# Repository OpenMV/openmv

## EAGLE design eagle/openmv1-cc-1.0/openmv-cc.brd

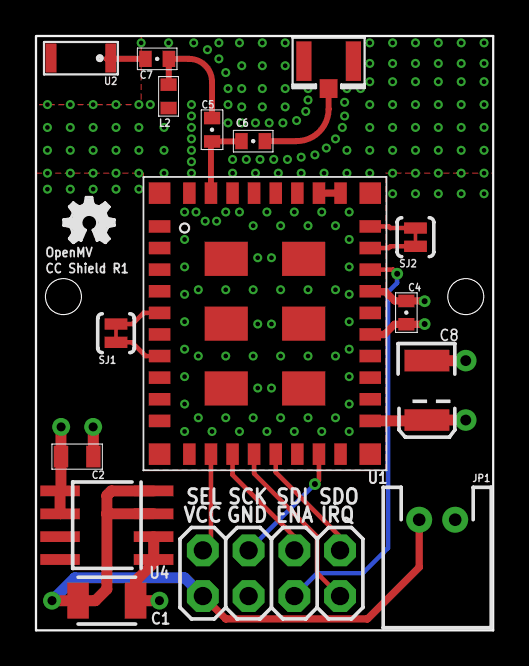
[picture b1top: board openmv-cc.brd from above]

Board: 4 copper layers, 25.4 x 33.0 mm, 17 parts (0 on the bottom side), 18 nets.

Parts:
C1: 47uF; 1210
C2: 10uF; 0805
C4: 1uF; 0402-CAP
C5, C6: 10pF; 0402-CAP
C7: 2.2pF; 0402-CAP
C8: 100uF; EIA3528
JP1: JP3; JST-2-PTH
L2: 2.2nH; C0402
LOGO1: OSHW_LOGO_FILLX0100-NT; OSHW_FILLX100_NOTEXT
SJ1, SJ2: SOLDERJUMPERTRACE; SJ_2S-TRACE
U1: CC3000
U2: ANT-YAGEO; ANTENNA
U3: U.FL
U4: TPS768; SOIC8
U5: OPENMV

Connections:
CC_CS: U1.P$12, U5.7
CC_EN: U1.P$26, U5.4
CC_IRQ: U1.P$14, U5.2
CC_MISO: U1.P$13, U5.3
CC_MOSI: U1.P$15, U5.1
CC_SCLK: U1.P$17, U5.5
GND: C1.2, C2.2, C4.2, C8.C, JP1.1, L2.2, U1.P$1, U1.P$9, U1.P$10, U1.P$11, U1.P$16, U1.P$18, U1.P$20, U1.P$21, U1.P$22, U1.P$25, U1.P$31, U1.P$32, U1.P$33, U1.P$34, U1.P$36, U1.P$37, U1.P$38, U1.P$39, U1.P$40, U1.P$41, U1.P$42, U1.P$43, U1.P$44, U1.P$45, U1.P$46, U3.P$1, U3.P$2, U4.1, U4.2, U5.6
unnamed: C5.1, C7.2, L2.1
unnamed: SJ1.2, U1.P$5
unnamed: SJ2.2, U1.P$28
unnamed: SJ1.1, U1.P$7
unnamed: SJ2.1, U1.P$27
unnamed: C5.2, C6.2, U1.P$35
unnamed: U1.P$29, U1.P$30
unnamed: C7.1, U2.P$1
unnamed: C6.1, U3.P$3
VCC: C2.1, C4.1, C8.A, U1.P$19, U1.P$23, U4.5, U4.6
VIN: C1.1, JP1.2, U4.3, U4.4, U5.8

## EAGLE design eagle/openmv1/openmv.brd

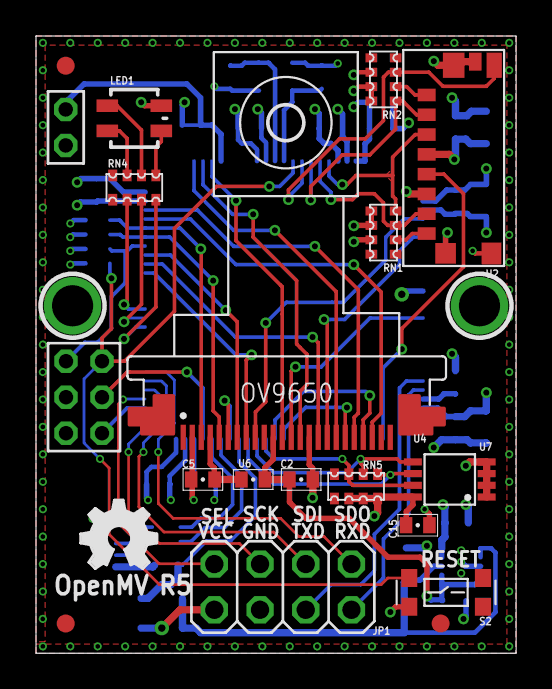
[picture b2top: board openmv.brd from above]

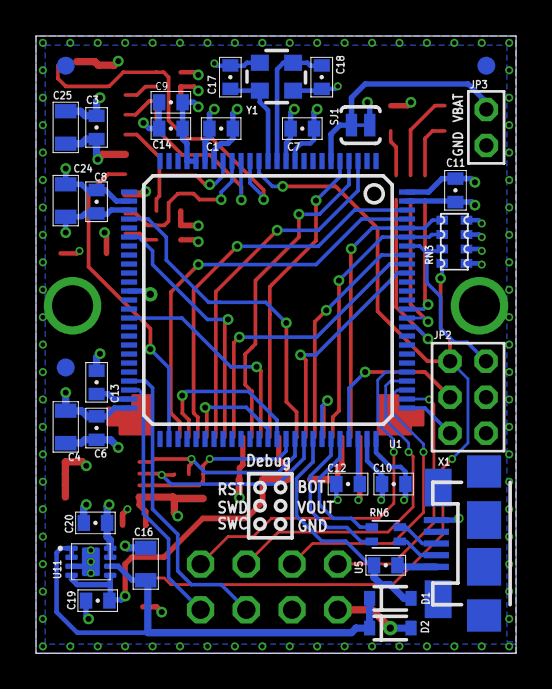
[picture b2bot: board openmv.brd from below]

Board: 4 copper layers, 26.7 x 34.3 mm, 52 parts (34 on the bottom side), 59 nets.

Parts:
C1, C3, C6, C7, C8, C9, C10, C11, C15: 0.1uF; 0402-CAP
C2, C5: 4.7uF; 0402-CAP
C4, C16, C24: 10uF; 0805
C12, C13: 2.2uF; 0402-CAP
C14, C19, C20: 1uF; 0402-CAP
C17, C18: 12pF; 0402-CAP
C25: 22uF; 0805
D1, D2: SOD-323
JP1: 2X04
JP2: 2X03
JP3: PINHD-1X2; 1X2
LED1: LED-TRICOLOR; LED-TRICOLOR-SMD
LOGO1: OSHW_LOGO_FILLX0150-NT; OSHW_FILLX150_NOTEXT
RN1, RN2, RN3, RN5: 10K; CAT16
RN4: 330R; CAT16
RN6: 27R; EXBV4V
S2: SWITCHKMR442G; KMR442G
SJ1: SOLDERJUMPERTRACE; SJ_2S-TRACE
U1: OV9650
U2: USD-47571
U4: STM32F407LQFP100; LQFP100
U5, U6: BEAD; 0402-CAP
U7: 24FC128; MSOP8
U11: ADP222; LFCSP8
U$3, U$4, U$5, U$7, U$9, U$10: FIDUCIAL; FIDUCIAL_1MM
X1: USB-MICROB
Y1: CRYSTAL-2.5X2.0

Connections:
2.8V: C2.1, C19.1, U1.P$11, U6.2, U11.4, U11.5
BOOT0: JP2.2, RN3.7, U4.94
DCMI0: U1.P$19, U4.63
DCMI1: U1.P$21, U4.64
DCMI2: U1.P$22, U4.97
DCMI3: U1.P$20, U4.98
DCMI4: U1.P$18, U4.3
DCMI5: U1.P$16, U4.92
DCMI6: U1.P$14, U4.4
DCMI7: U1.P$12, U4.5
EEP_SCL: RN5.1, U4.67, U7.6
EEP_SDA: RN5.2, U4.66, U7.5
EEP_WP: RN5.3, U4.65, U7.7
FS_DM: RN6.2, U4.70
FS_DP: RN6.1, U4.71
GND: C1.1, C2.2, C3.2, C4.1, C5.2, C6.1, C7.2, C8.1, C9.1, C10.2, C11.2, C12.2, C13.2, C14.1, C15.2, C16.2, C17.2, C18.2, C19.2, C20.2, C24.1, C25.2, JP1.6, JP2.6, JP3.1, RN3.2, S2.P$3, U1.P$2, U1.P$15, U2.G$1, U2.G$2, U2.G$3, U2.G$4, U2.P$6, U4.10, U4.20, U4.27, U4.37, U4.74, U4.99, U7.1, U7.2, U7.3, U7.4, U11.3, U11.EXP, X1.GND, Y1.2, Y1.4
HSYNC: U1.P$9, U4.29
I2C1_SCL: RN3.6, U1.P$5, U4.95
I2C1_SDA: RN3.5, U1.P$3, U4.96
I2C2_SCL: JP1.4, U4.47
I2C2_SDA: JP1.2, U4.48
LED_B: RN4.7, U4.86
LED_G: RN4.6, U4.87
LED_R: RN4.8, U4.85
unnamed: RN1.6, U2.P$8
unnamed: RN2.6, U2.P$1
unnamed: LED1.R, RN4.1
unnamed: LED1.G, RN4.3
unnamed: LED1.B, RN4.2
unnamed: C17.1, U4.13, Y1.3
unnamed: RN6.3, X1.D-
unnamed: C18.1, U4.12, Y1.1
unnamed: C5.1, U1.P$4, U6.1
unnamed: RN6.4, X1.D+
unnamed: U5.1, X1.VBUS
NRST: JP2.1, RN3.8, S2.P$1, U4.14
PCLK: U1.P$17, U4.31
PWDN: U1.P$8, U4.91
RAW: D2.2, JP1.8
RESET: U1.P$6, U4.69
SD_CD: RN2.7, U2.G$5, U4.15
SD_MISO: RN1.7, U2.P$7, U4.17
SD_MOSI: RN1.8, U2.P$3, U4.18
SD_SCLK: U2.P$5, U4.52
SD_SSEL: RN2.5, U2.P$2, U4.16
SPI3_MISO: JP1.3, U4.79
SPI3_MOSI: JP1.1, U4.80
SPI3_SCLK: JP1.5, U4.78
SPI3_SSEL: JP1.7, U4.77
SWCLK: JP2.5, U4.76
SWDIO: JP2.3, U4.72
VBAT: JP3.2, SJ1.1, U4.6
VBUS: D1.2, U4.68, U5.2
VCAP1: C13.1, U4.49
VCAP2: C12.1, U4.73
VCC: C1.2, C3.1, C4.2, C6.2, C7.1, C8.2, C9.2, C10.1, C11.1, C14.2, C15.1, C20.1, C24.2, C25.1, JP2.4, LED1.A, RN1.1, RN1.2, RN1.3, RN2.2, RN2.3, RN2.4, RN3.1, RN3.3, RN3.4, RN5.6, RN5.7, RN5.8, SJ1.2, U2.P$4, U4.11, U4.19, U4.21, U4.22, U4.28, U4.50, U4.75, U4.100, U7.8, U11.7, U11.8
VIN: C16.1, D1.1, D2.1, U11.1, U11.2, U11.6
VSYNC: U1.P$7, U4.93
XCLK: U1.P$13, U4.40

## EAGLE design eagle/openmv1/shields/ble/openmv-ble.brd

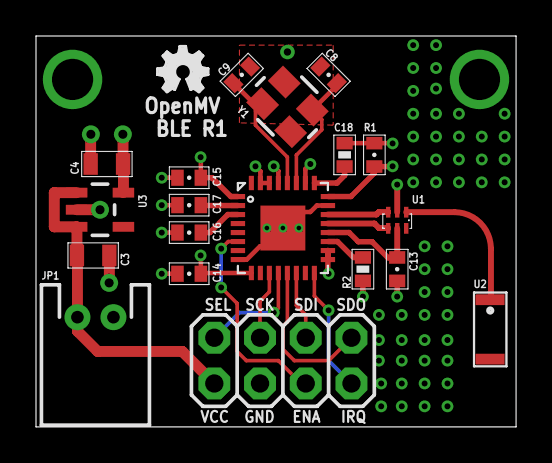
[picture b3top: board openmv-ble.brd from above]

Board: 4 copper layers, 26.7 x 21.7 mm, 20 parts (0 on the bottom side), 19 nets.

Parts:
C3, C4: 10uF; 0805
C8, C9: 22pF; 0402-CAP
C13: 2.2nF; 0402-CAP
C14, C15, C16: 0.1uF; 0402-CAP
C17: 0.33uF; 0402-CAP
C18: 0.01uF; 0402-CAP
JP1: JP3; JST-2-PTH
LOGO1: OSHW_LOGO_FILLX0100-NT; OSHW_FILLX100_NOTEXT
R1: 22k; 0402-RES
R2: 10k; 0402-RES
U1: 2450BM14A0002
U2: ANT-YAGEO; ANTENNA
U3: 2.8V; SOT23-5
U5: OPENMVSMALL; OPENMV-SMALL
U$2: NRF8001; QFN-32
Y1: 16Mhz; CRYSTAL3.2X2.5

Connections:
ACTIVE: U5.4, U$2.P$6
GND: C3.2, C4.2, C8.2, C9.2, C13.2, C14.2, C15.2, C16.2, C17.2, C18.2, JP1.1, R1.1, U1.P$2, U3.2, U5.6, U$2.P$8, U$2.P$17, U$2.P$18, U$2.P$23, U$2.P$30, U$2.P$31, U$2.P$33, Y1.2, Y1.4
MISO: U5.3, U$2.P$14
MOSI: U5.1, U$2.P$13
unnamed: C9.1, U$2.P$28, Y1.3
unnamed: C8.1, U$2.P$27, Y1.1
unnamed: U1.P$3, U$2.P$22
unnamed: U1.P$1, U2.P$1
unnamed: U1.P$4, U$2.P$21
unnamed: C13.1, U1.P$5, U$2.P$20
unnamed: C17.1, U$2.P$2
unnamed: C16.1, U$2.P$3
unnamed: R1.2, U$2.P$25
unnamed: R2.2, U$2.P$19
RDY: U5.2, U$2.P$16
REQ: U5.7, U$2.P$12
SCLK: U5.5, U$2.P$11
VCC: C4.1, C14.1, C15.1, C18.1, R2.1, U3.5, U$2.P$1, U$2.P$9, U$2.P$24, U$2.P$26, U$2.P$29
VIN: C3.1, JP1.2, U3.1, U3.3, U5.8

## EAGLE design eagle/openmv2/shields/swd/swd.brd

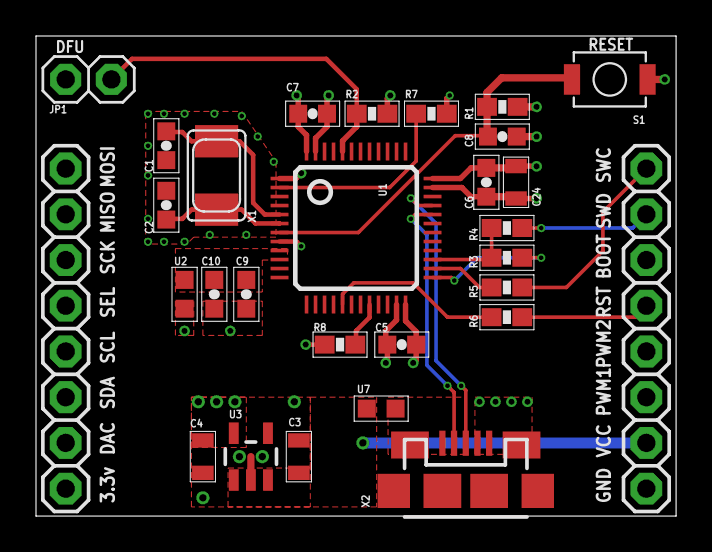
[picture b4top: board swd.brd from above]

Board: 4 copper layers, 35.6 x 26.7 mm, 28 parts (0 on the bottom side), 20 nets.

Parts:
C1, C2: 18pF; 0603-CAP
C3, C4, C24: 10uF; 0805
C5, C6, C7, C8, C9: 0.1uF; 0603-CAP
C10: 1uF; 0603-CAP
JP1: 1X02
R1, R2, R7, R8: 10K; 0603-RES
R3: 100R; 0603-RES
R4, R5, R6: 33R; 0603-RES
S1: SPST_3X4X2; 3X4X2TACT
U1: STM32F103C8T6; LQFP48
U2, U7: 0603
U3: 3.3v; SOT23-5
U$2: OPENMV3
X1: 8MHz; NX5032
X2: USB-MICROB

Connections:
3V3: C4.1, C5.2, C6.2, C7.2, C24.2, JP1.1, R1.1, U1.1, U1.24, U1.36, U1.48, U2.2, U3.5
BOOT0: JP1.2, R2.2, U1.44
BOOT1: R8.2, U1.20
FS_DM: U1.32, X2.D-
FS_DP: U1.33, X2.D+
GND: C1.1, C2.1, C3.2, C4.2, C5.1, C6.1, C7.1, C8.1, C9.1, C10.1, C24.1, R2.1, R7.2, R8.1, S1.P$1, U1.8, U1.23, U1.35, U1.47, U3.2, U$2.28, X2.GND
unnamed: R5.2, U$2.21
unnamed: R7.1, U1.2
unnamed: R4.2, U$2.22
unnamed: R6.2, U$2.24
unnamed: C1.2, U1.5, X1.P$1
unnamed: U7.1, X2.VBUS
unnamed: C2.2, U1.6, X1.P$2
NRST: C8.2, R1.2, S1.P$2, U1.7
T_NRST: R6.1, U1.17
T_SWC: R5.1, U1.26
T_SWD: R3.2, R4.1, U1.27
T_SWD_IN: R3.1, U1.25
VBUS: C3.1, U3.1, U3.3, U7.2, U$2.27
VDDA: C9.2, C10.2, U1.9, U2.1

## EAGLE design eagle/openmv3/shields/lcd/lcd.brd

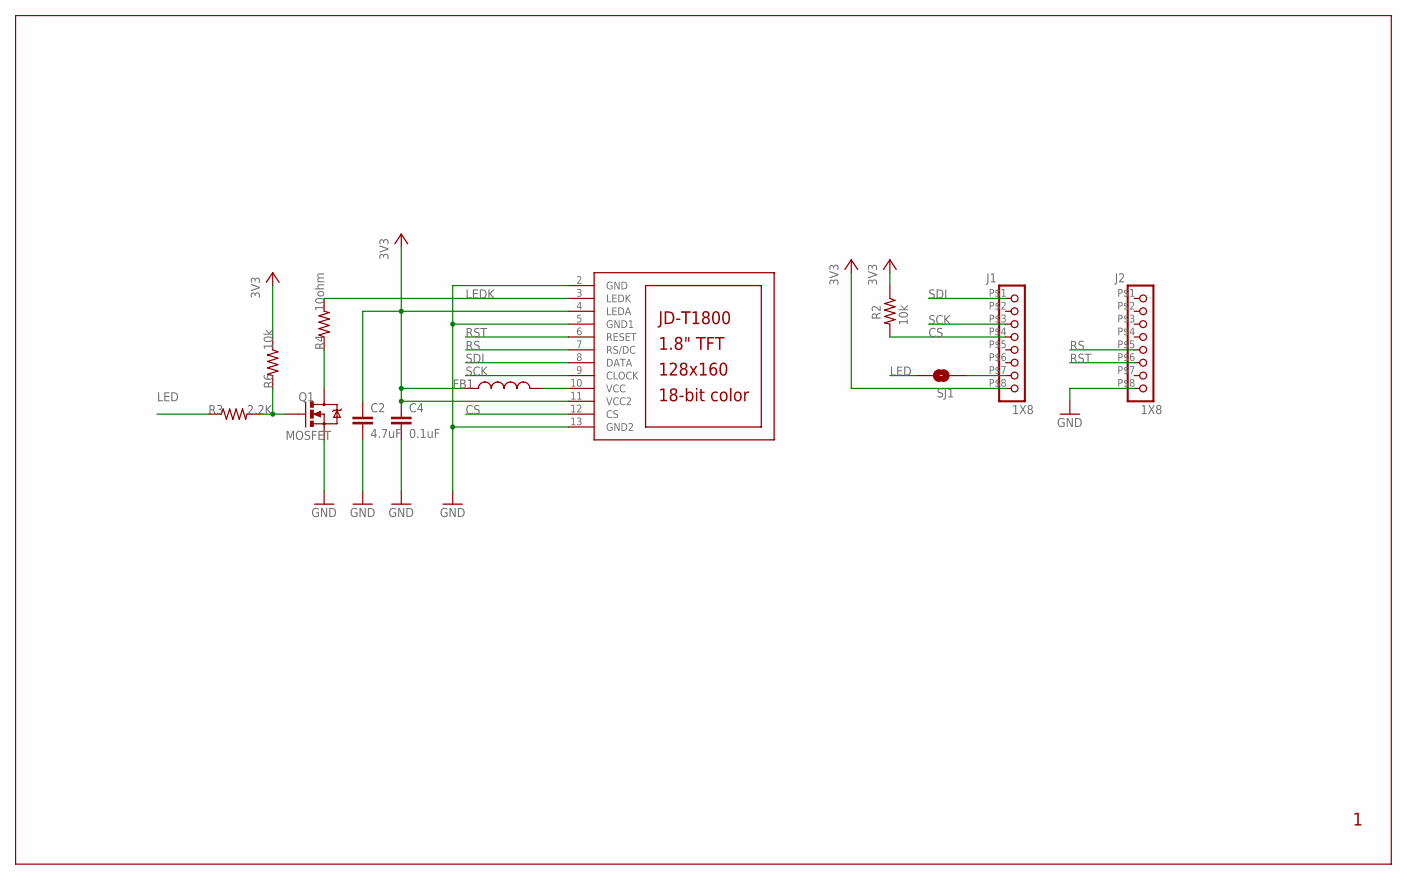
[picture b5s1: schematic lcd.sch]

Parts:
C2: 4.7uF; 0603-CAP
C4: 0.1uF; 0603-CAP
FB1: INDUCTOR0603; 0603
J1, J2: 1X8
LCD1: JD-T1800
Q1: MOSFET; SOT23-3
R2, R6: 10k; 0603-RES
R3: 2.2K; 0603-RES
R4: 10ohm; 0603-RES
SJ1: SOLDERJUMPERTRACE; SJ_2S-TRACE

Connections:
3V3: C2.1, C4.1, FB1.1, J1.P$8 (8), LCD1.4 (LEDA), LCD1.11 (VCC2), R2.1, R6.1
CS: J1.P$4 (4), LCD1.12 (CS), R2.2
GND: C2.2, C4.2, J2.P$8 (8), LCD1.2 (GND), LCD1.5 (GND1), LCD1.13 (GND2), Q1.2 (S)
LED: R3.1, SJ1.2
LEDK: LCD1.3 (LEDK), R4.2
unnamed: J1.P$7 (7), SJ1.1
unnamed: Q1.1 (G), R3.2, R6.2
unnamed: Q1.3 (D), R4.1
RS: J2.P$5 (5), LCD1.7 (RS/DC)
RST: J2.P$6 (6), LCD1.6 (RESET)
SCK: J1.P$3 (3), LCD1.9 (CLOCK)
SDI: J1.P$1 (1), LCD1.8 (DATA)
VDDA: FB1.2, LCD1.10 (VCC)

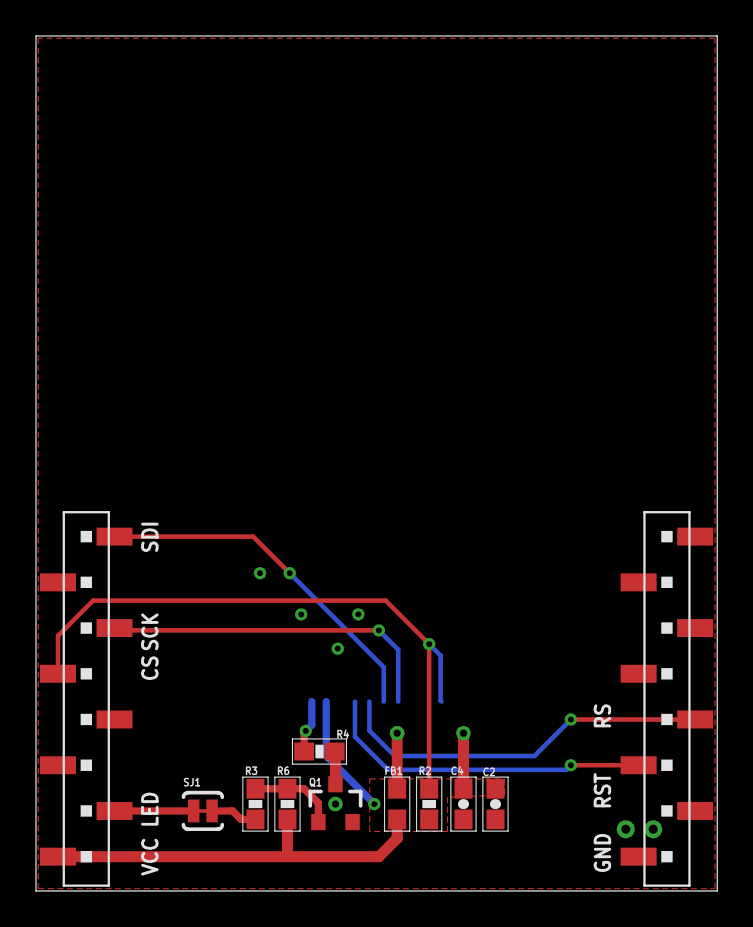
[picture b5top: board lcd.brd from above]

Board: 2 copper layers, 37.8 x 47.5 mm, 12 parts (1 on the bottom side), 13 nets.

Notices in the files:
eagle/openmv2/shields/lcd/lcd.sch:
Copyright (c) 2013 Ibrahim Abd Elkader
This work is licensed under the Creative Commons Attribution-ShareAlike 3.0 License.
To view a copy of this license, visit http://creativecommons.org/licenses/by-sa/3.0
